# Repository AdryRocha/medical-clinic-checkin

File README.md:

# medical-clinic-checkin
Repositório com o desenvolvimento de código embarcado, utilizando a linguagem C++, para funcionalidades de check-in em clínicas médicas, baseado em Raspberry Pi Pico W. O sistema integra tecnologias de Sistemas Embarcados de Tempo Real (RTOS), Visão Computacional, Biometria e Integração Cloud em uma arquitetura robusta e escalável.

# Arquitetura de Branches (Estratégia de Hardware)

Para atender a diferentes requisitos de custo e segurança, o projeto está segmentado em três implementações principais:

| Branch | Foco Tecnológico	| Diferencial de Engenharia |
|------|---------|---------|
| rp2040 |	Eficiência & Custo | Otimização para Dual-Core ARM Cortex-M0+ e gestão rigorosa de 264KB de RAM |
| rp2350 |	Performance & Segurança	| Utilização de ARM Cortex-M33, aceleração de ponto flutuante (FPU) e isolamento TrustZone |
| api |	Integração & Cloud | Gateway de comunicação REST e gestão de templates biométricos via PostgreSQL |

Para alternar entre estas implementações, basta executar o seguinte comando no seu terminal:

```
git checkout <nome-da-branch>
```

##
| Branch | Foco Tecnológico	| Diferencial de Engenharia |
|------|---------|---------|
| Camada | Tecnologia | Justificativa Técnica |
| KernelFreeRTOS | Garante determinismo nas tarefas de UI e validação de biometria.
| Interface (GUI) | LVGL v8.3.11 | Motor gráfico otimizado para hardware limitado com suporte a antialiasing.
| Persistência | FatFS (SD Card) | | Sistema de arquivos resiliente para armazenamento de logs e agendamentos offline. | 
| Parsing | cJSON | Manipulação eficiente de objetos JSON provenientes da leitura de QR Codes. | 
| Build System | CMake + Ninja | Automação de build multiplataforma e gestão de dependências via FetchContent. |

---

## Visão Geral

| Item | Detalhe |
|------|---------|
| **MCU** | RP2040W — Dual-core ARM Cortex-M0+ @ 133 MHz, WiFi CYW43439 |
| **MCU** | RP2350W — Dual-core ARM Cortex-M33 ou RISCO-V @ 150 MHz, ARM TrustZone, OTP |
| **RTOS** | FreeRTOS (5 tasks, queues, event groups) |
| **UI** | LVGL v8.3.11 — 7 telas, ícones desenhados via código |
| **Linguagem** | C++17 / C11 |
| **Build** | CMake ≥ 3.13 + Ninja 1.12.1 + GCC ARM 14_2_Rel1 |

**Funcionalidades principais:**
- Leitura de QR Code via scanner GM67 (UART)
- Validação de agendamento com dados armazenados no SD Card (FatFS)
- Verificação e cadastro de impressão digital via sensor R307S
- Sincronização de agendamentos e templates biométricos com API REST (Mongoose HTTP)
- Sincronização de hora via NTP (SNTP/lwIP)
- Interface touchscreen 4.0" 480×320

---

## Hardware

| Periférico | Interface | Pinos |
|-----------|-----------|-------|
| Display ST7796 4.0" TFT 480×320 | SPI0 | MOSI=GP19, SCK=GP18, CS=GP17, DC=GP20, RST=GP21 |
| Touch FT6336U (Capacitivo) | I2C1 | SDA=GP6, SCL=GP7, RST=GP8, INT=GP9 |
| Scanner QR GM67 | UART0 | TX=GP0, RX=GP1 |
| Sensor Biométrico R307S | UART1 | TX=GP4, RX=GP5 |
| SD Card (FAT32) | SPI1 | MISO=GP12, MOSI=GP15, SCK=GP14, CS=GP13 |
| WiFi CYW43439 | Integrado | — |

---

## Arquitetura de Software

O software foi projetado seguindo o padrão de Camadas de Abstração de Hardware (HAL), permitindo portabilidade total entre RP2040 e RP2350:

### Tasks FreeRTOS

| Task | Prioridade | Stack | Responsabilidade |
|------|:----------:|:-----:|------------------|
| `WiFi_Time_Init` | 5 | 2048 | Conecta WiFi, sincroniza NTP, auto-deleta após sucesso |
| `LVGL` | 4 | 3072 | `lv_timer_handler()` a cada 20 ms, gerencia telas por estado |
| `QR_Reader` | 3 | 1536 | Leitura contínua do GM67, envia dados para fila |
| `QR_Validator` | 2 | 2048 | Valida QR, biometria, marca check-in (orquestrador) |
| `Network` | 2 | 3072 | Download de agendamentos/templates, atualiza status na API |

### Services (Singletons)

| Service | Função |
|---------|--------|
| `AppointmentService` | Valida QR JSON, busca agendamento no SD, verifica CPF e janela de horário (−20/+10 min) |
| `NetworkSyncService` | Cliente HTTP (Mongoose): autenticação JWT, download/upload de agendamentos e templates |
| `DataStorageService` | Lê/grava JSON de agendamentos e templates `.dat` de fingerprint no SD Card (FatFS) |
| `TimeService` | Sincroniza NTP → RTC do RP2040, fornece data/hora formatadas |
| `FingerprintService` | Cadastro (2 capturas → template → SD + API) e verificação de digitais via R307S |

---

## Estrutura do Projeto

```
├── CMakeLists.txt
├── pico_sdk_import.cmake
│
├── config/
│   ├── api_config.hpp                  # URL da API, endpoints, credenciais, timeouts
│   ├── display_config.hpp              # Resolução, rotação, SPI speed, buffer LVGL
│   ├── fingerprint_config.hpp          # UART e baudrate do sensor biométrico
│   ├── FreeRTOSConfig.h                # Configuração do kernel FreeRTOS
│   ├── hw_config.c                     # Configuração do SD Card (FatFS)
│   ├── lv_conf.h                       # Configuração do LVGL
│   ├── lvgl_tick_custom.h              # Tick customizado do LVGL para FreeRTOS
│   ├── lwipopts.h                      # Configuração do lwIP (TCP/IP stack)
│   ├── mongoose_config.h               # Configuração do Mongoose HTTP
│   ├── pin_config.hpp                  # Mapeamento de todos os GPIOs
│   ├── qr_code_reader_config.hpp       # UART e baudrate do scanner QR
│   ├── sntp_callbacks.h                # Callbacks de sincronização NTP
│   └── wifi_config.hpp                 # SSID, senha e país do WiFi
│
├── src/
│   ├── main.cpp                        # Entry point: init drivers → create tasks → scheduler
│   │
│   ├── core/
│   │   ├── state_machine.hpp           # Máquina de estados (singleton, 11 estados)
│   │   └── state_machine.cpp
│   │
│   ├── hal/
│   │   ├── interfaces/
│   │   │   ├── hal_spi_interface.hpp   # Interface abstrata SPI
│   │   │   ├── hal_i2c_interface.hpp   # Interface abstrata I2C
│   │   │   ├── hal_uart_interface.hpp  # Interface abstrata UART
│   │   │   └── hal_wifi_interface.hpp  # Interface abstrata WiFi
│   │   └── rp2040/
│   │       ├── hal_spi_rp2040.hpp/.cpp
│   │       ├── hal_i2c_rp2040.hpp/.cpp
│   │       ├── hal_uart_rp2040.hpp/.cpp
│   │       └── hal_wifi_rp2040.hpp/.cpp
│   │
│   ├── drivers/
│   │   ├── display/
│   │   │   ├── interface/display_interface.hpp
│   │   │   └── st7796/st7796_driver.hpp/.cpp
│   │   ├── touch/
│   │   │   ├── interface/touch_interface.hpp
│   │   │   └── ft6336u/ft6336u_driver.hpp/.cpp
│   │   ├── qr_code_reader/
│   │   │   ├── interface/qr_interface.hpp
│   │   │   └── gm67/gm67_driver.hpp/.cpp
│   │   └── fingerprint/
│   │       ├── interface/fingerprint_interface.hpp
│   │       └── r307s/r307s_driver.hpp/.cpp
│   │
│   ├── adapters/lvgl/
│   │   ├── lvgl_display_adapter.hpp/.cpp
│   │   └── lvgl_touch_adapter.hpp/.cpp
│   │
│   ├── services/
│   │   ├── appointment_service.hpp/.cpp     # Validação de QR e agendamentos
│   │   ├── data_storage_service.hpp/.cpp    # Leitura/escrita no SD Card
│   │   ├── fingerprint_service.hpp/.cpp     # Cadastro e verificação biométrica
│   │   ├── network_sync_service.hpp/.cpp    # Cliente HTTP (Mongoose)
│   │   └── time_service.hpp/.cpp            # NTP → RTC, data/hora
│   │
│   ├── tasks/
│   │   ├── task_wifi_time_init.hpp/.cpp     # Conexão WiFi + sincronização NTP
│   │   ├── task_lvgl.hpp/.cpp               # Loop LVGL + gerência de telas
│   │   ├── task_qr_reader.hpp/.cpp          # Leitura contínua do scanner QR
│   │   ├── task_qr_validator.hpp/.cpp       # Validação e orquestração do check-in
│   │   └── task_network.hpp/.cpp            # Download de agendamentos e templates
│   │
│   ├── ui/screens/
│   │   ├── welcome_screen.hpp/.cpp          # Tela principal (idle)
│   │   ├── init_status_screen.hpp/.cpp      # Tela de boot (WiFi, NTP, SD)
│   │   ├── appointment_screen.hpp/.cpp      # Check-in confirmado
│   │   ├── error_screen.hpp/.cpp            # Erro recuperável
│   │   ├── error_critical_screen.hpp/.cpp   # Erro crítico + countdown reboot
│   │   ├── fingerprint_operation_screen.hpp/.cpp  # Verificação/cadastro digital
│   │   └── fingerprint_upload_screen.hpp/.cpp     # Upload de template
│   │
│   └── tests/code_examples/
│       ├── README.md                        # Instruções dos demos
│       ├── lvgl_rtos_demo.cpp               # Demo display + touch
│       ├── qr_code_reader_demo.cpp          # Demo scanner QR
│       ├── fingerprint_demo.cpp             # Demo sensor biométrico
│       ├── sdcard_fatfs_demo.cpp            # Demo SD Card
│       └── wifi_demo.cpp                    # Demo WiFi
│
├── lib/
│   ├── FreeRTOS-Kernel/                     # Submodule
│   └── no-OS-FatFS/                         # Submodule
│
└── docs/
    ├── dev/                                 # Notas de desenvolvimento por periférico
    └── diagrams/
        ├── hardware_diagram.md
        ├── software_architecture_layers_diagram.md
        ├── class_diagrams.md
        ├── sequence_diagrams.md
        └── state_machine_diagram.md
```
### Licença & Uso
## Este projeto está licenciado sob a MIT License. Sinta-se à vontade para explorar, modificar e contribuir, mantendo os créditos originais.
---

---
## Projeto desenvolvido como parte da Residência Tecnológica em Sistemas Embarcadosdo, do programa EmbarcaTech - Polo Campinas/SP.
---

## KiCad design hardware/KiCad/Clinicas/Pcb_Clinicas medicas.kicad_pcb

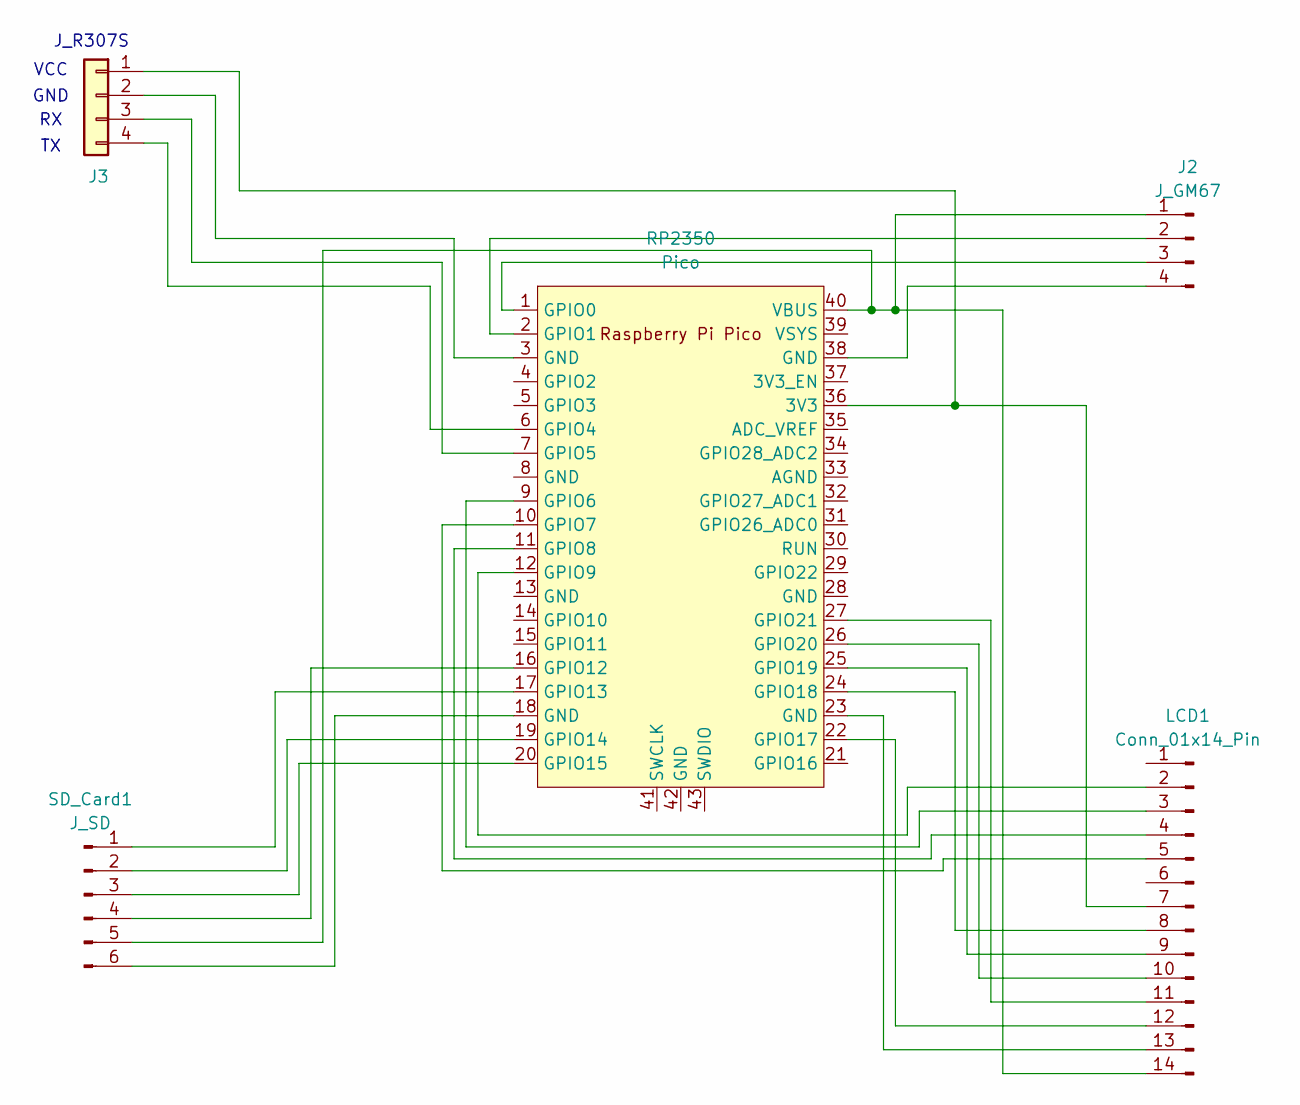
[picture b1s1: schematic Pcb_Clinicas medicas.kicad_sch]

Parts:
J2: J_GM67; PinHeader_1x04_P2.54mm_Vertical
J3: Conn_01x04; PinHeader_1x04_P2.54mm_Vertical
LCD1: Conn_01x14_Pin; PinHeader_1x14_P2.54mm_Vertical
RP2350: Pico; RaspberryPi_Pico_Common_THT
SD_Card1: J_SD; PinHeader_1x06_P2.54mm_Vertical

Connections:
unnamed: J2.1, LCD1.14, RP2350.40 (VBUS), SD_Card1.5
unnamed: J2.2, RP2350.2 (GPIO1)
unnamed: J2.3, RP2350.1 (GPIO0)
unnamed: J2.4, RP2350.38 (GND)
unnamed: J3.1, LCD1.7, RP2350.36 (3V3)
unnamed: J3.2, RP2350.3 (GND)
unnamed: J3.3, RP2350.7 (GPIO5)
unnamed: J3.4, RP2350.6 (GPIO4)
unnamed: LCD1.2, RP2350.12 (GPIO9)
unnamed: LCD1.3, RP2350.9 (GPIO6)
unnamed: LCD1.4, RP2350.11 (GPIO8)
unnamed: LCD1.5, RP2350.10 (GPIO7)
unnamed: LCD1.8, RP2350.24 (GPIO18)
unnamed: LCD1.9, RP2350.25 (GPIO19)
unnamed: LCD1.10, RP2350.26 (GPIO20)
unnamed: LCD1.11, RP2350.27 (GPIO21)
unnamed: LCD1.12, RP2350.22 (GPIO17)
unnamed: LCD1.13, RP2350.23 (GND)
unnamed: RP2350.16 (GPIO12), SD_Card1.4
unnamed: RP2350.17 (GPIO13), SD_Card1.1
unnamed: RP2350.19 (GPIO14), SD_Card1.2
unnamed: RP2350.20 (GPIO15), SD_Card1.3
unnamed: RP2350.18 (GND), SD_Card1.6

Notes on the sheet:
J_R307S
GND
VCC

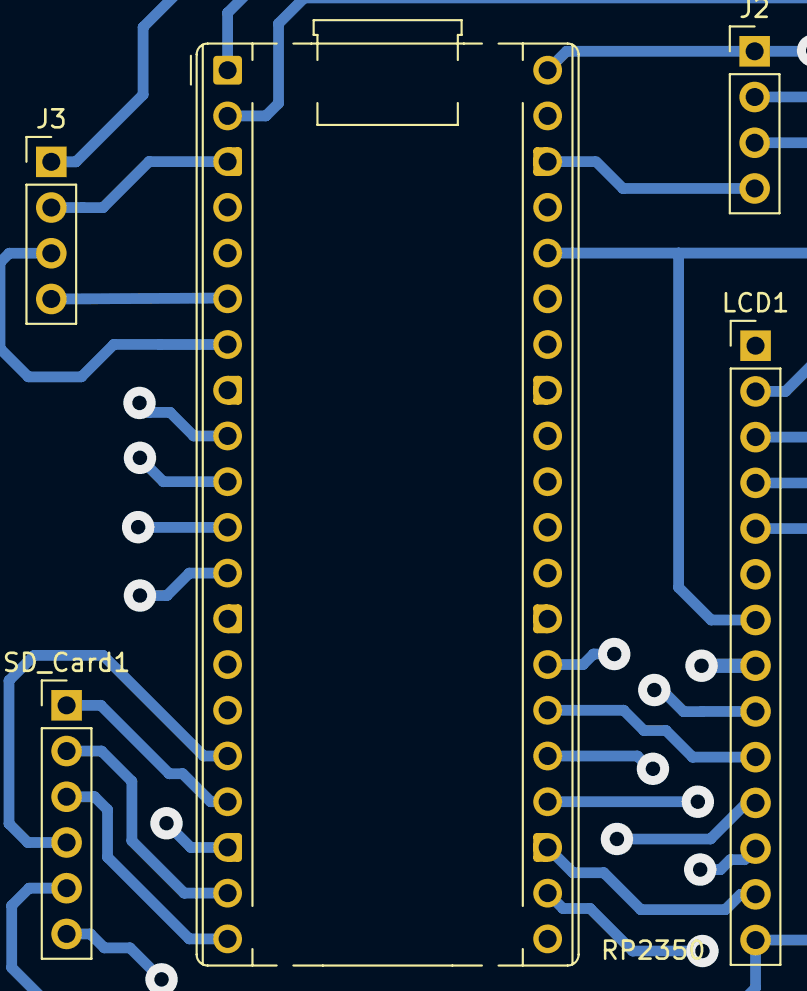
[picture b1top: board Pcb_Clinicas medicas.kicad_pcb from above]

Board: 2 copper layers, 5 parts (0 on the bottom side), 23 nets.

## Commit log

2026-02-22 Update README to include branch information
    Add explanation about protected branches in the repository.
2026-02-22 Adiciona bibliotecas, pasta build e atualiza README
2026-02-22 Adiciona arquivos de configuracoes dos modulos do projeto
2026-02-22 Adiciona arquivos para cmake
2026-02-22 Adiciona documentacao do repositorio
2026-02-22 Adiciona codigo principal
2026-02-22 Adiciona arquivos fonte, documentos e configuracoes para a placa rp2350
2026-02-22 Adiciona arquivos para rodar a api
2026-02-24 autoras
2026-02-24 Update README with project versions and authors
    Added project version details and authors section.
2026-02-24 Update README with repository structure and branches
    Added repository organization details and branch information.
2026-02-25 Revise README with enhanced project overview and structure
    Updated project description and branch architecture details for clarity and added technical justification for technology choices.
2026-02-25 Refactor README.md for better structure and clarity
    Updated the README.md to improve formatting and clarity, including restructuring tables and sections.
2026-02-25 Remove hardware diagram link from README
    Removed link to hardware diagram in README.
2026-02-25 Remove architecture diagram from README
    Removed detailed architecture diagram for software layers.
2026-02-25 Refactor README structure and headings
2026-02-25 Add contributor Luana Menezes to README
2026-02-25 Initialize g_lvgl_mutex for LVGL mutex
2026-02-26 Remove developer names section from README
    Removed developer names from the README file.
2026-02-26 Add RP2350W MCU details to README
2026-02-27 Ignore build artifacts
2026-02-27 Add FreeRTOS-Kernel and no-OS-FatFS as submodules
2026-03-01 Sanitize configs, ignore build/media, update docs (rp2040)
2026-03-01 Small fixes on rp2040
2026-03-09 Change CPU model in hardware diagram
    Updated CPU model in hardware diagram from RP2040W to RP2350W.
2026-03-09 Fix link formatting in README.md
2026-03-09 Update README to specify C++ usage
